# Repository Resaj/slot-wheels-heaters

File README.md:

# Slot wheels heaters
Wheels heaters for slot cars or line-following robots.

Each wheel heater carries a thermistor and is composed of an array of 25 resistor in parallel. The value of each resistance is 470 Ohm and the supply is a lipo battery 2S. Changing this values may burn the heaters, so if you change the values be sure the power consume values are right.

## Author
[Rubén Espino San José](https://github.com/Resaj)

## License

Todos estos productos están liberados mediante [Creative Commons Attribution-ShareAlike 4.0 International License](http://creativecommons.org/licenses/by-sa/4.0/).  
_All these products are released under [Creative Commons Attribution-ShareAlike 4.0 International License](http://creativecommons.org/licenses/by-sa/4.0/)._

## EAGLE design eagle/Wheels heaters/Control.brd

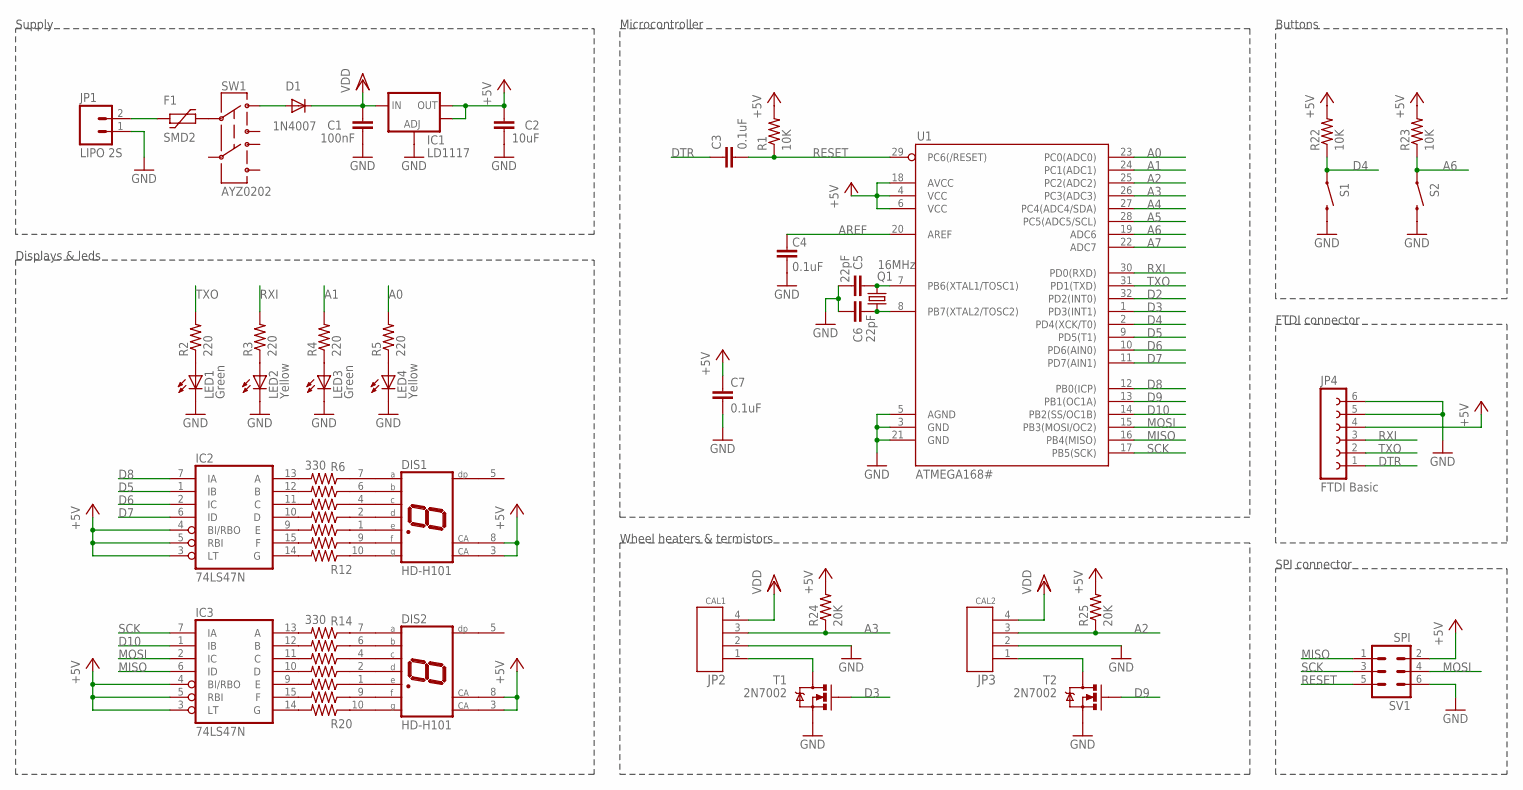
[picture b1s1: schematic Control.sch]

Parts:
C1: 100nF; C0805
C2: 10uF; C0805
C3, C4, C7: 0.1uF; C0805
C5, C6: 22pF; C0805
D1: 1N4007; SOD106-R
DIS1, DIS2: HD-H101; HDSP-M
F1: SMD2
IC1: LD1117; SOT223
IC2, IC3: 74LS47N; DIL16
JP1: LIPO 2S; 1X02
JP2: CAL1; 4_PINES_MACHO_TUMBADOS
JP3: CAL2; 4_PINES_MACHO_TUMBADOS
JP4: FTDI Basic; FE06W
LED1, LED3: Green; LED3MM
LED2, LED4: Yellow; LED3MM
Q1: 16MHz; HC49/S
R1, R22, R23: 10K; R0805
R2, R3, R4, R5: 220; R0805
R6, R7, R8, R9, R10, R11, R12, R14, R15, R16, R17, R18, R19, R20: 330; R0805
R24, R25: 20K; R0805
S1, S2: SWITCH-MOMENTARY-2PTH; TACTILE-PTH
SV1: SPI; MA03-2
SW1: AYZ0202
T1, T2: 2N7002; SOT23-3
U1: ATMEGA168#; TQFP32-08

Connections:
+5V: C2.1, C7.1, DIS1.3 (CA), DIS1.8 (CA), DIS2.3 (CA), DIS2.8 (CA), IC1.2 (OUT), IC1.4 (OUT), IC2.3 (LT), IC2.4 (BI/RBO), IC2.5 (RBI), IC2.16 (VCC), IC3.3 (LT), IC3.4 (BI/RBO), IC3.5 (RBI), IC3.16 (VCC), JP4.4, R1.2, R22.2, R23.2, R24.2, R25.2, SV1.2, U1.4 (VCC), U1.6 (VCC), U1.18 (AVCC)
A0: R5.2, U1.23 (PC0(ADC0))
A1: R4.2, U1.24 (PC1(ADC1))
A2: JP3.3, R25.1, U1.25 (PC2(ADC2))
A3: JP2.3, R24.1, U1.26 (PC3(ADC3))
A4: U1.27 (PC4(ADC4/SDA))
A5: U1.28 (PC5(ADC5/SCL))
A6: R23.1, S2.1, U1.19 (ADC6)
A7: U1.22 (ADC7)
AREF: C4.2, U1.20 (AREF)
D2: U1.32 (PD2(INT0))
D3: T1.1 (G), U1.1 (PD3(INT1))
D4: R22.1, S1.1, U1.2 (PD4(XCK/T0))
D5: IC2.1 (IB), U1.9 (PD5(T1))
D6: IC2.2 (IC), U1.10 (PD6(AIN0))
D7: IC2.6 (ID), U1.11 (PD7(AIN1))
D8: IC2.7 (IA), U1.12 (PB0(ICP))
D9: T2.1 (G), U1.13 (PB1(OC1A))
D10: IC3.1 (IB), U1.14 (PB2(SS/OC1B))
DTR: C3.1, JP4.1
GND: C1.1, C2.2, C4.1, C5.1, C6.1, C7.2, IC1.1 (ADJ), IC2.8 (GND), IC3.8 (GND), JP1.1, JP2.2, JP3.2, JP4.5, JP4.6, LED1.K (C), LED2.K (C), LED3.K (C), LED4.K (C), S1.3 (2), S2.3 (2), SV1.6, T1.2 (S), T2.2 (S), U1.3 (GND), U1.5 (AGND), U1.21 (GND)
MISO: IC3.6 (ID), SV1.1, U1.16 (PB4(MISO))
MOSI: IC3.2 (IC), SV1.4, U1.15 (PB3(MOSI/OC2))
unnamed: C6.2, Q1.2, U1.8 (PB7(XTAL2/TOSC2))
unnamed: C5.2, Q1.1, U1.7 (PB6(XTAL1/TOSC1))
unnamed: JP2.1, T1.3 (D)
unnamed: JP3.1, T2.3 (D)
unnamed: LED2.A, R3.1
unnamed: LED3.A, R4.1
unnamed: D1.A, SW1.3 (1)
unnamed: F1.P$2 (2), SW1.2
unnamed: F1.P$1 (1), JP1.2
unnamed: LED4.A, R5.1
unnamed: LED1.A, R2.1
unnamed: IC2.13 (A), R6.2
unnamed: DIS1.7 (A), R6.1
unnamed: IC2.12 (B), R7.2
unnamed: DIS1.6 (B), R7.1
unnamed: IC2.11 (C), R8.2
unnamed: DIS1.4 (C), R8.1
unnamed: IC2.10 (D), R9.2
unnamed: DIS1.2 (D), R9.1
unnamed: IC2.9 (E), R10.2
unnamed: DIS1.1 (E), R10.1
unnamed: IC2.15 (F), R11.2
unnamed: DIS1.9 (F), R11.1
unnamed: IC2.14 (G), R12.2
unnamed: DIS1.10 (G), R12.1
unnamed: IC3.13 (A), R14.2
unnamed: DIS2.7 (A), R14.1
unnamed: IC3.12 (B), R15.2
unnamed: DIS2.6 (B), R15.1
unnamed: IC3.11 (C), R16.2
unnamed: DIS2.4 (C), R16.1
unnamed: IC3.10 (D), R17.2
unnamed: DIS2.2 (D), R17.1
unnamed: IC3.9 (E), R18.2
unnamed: DIS2.1 (E), R18.1
unnamed: IC3.15 (F), R19.2
unnamed: DIS2.9 (F), R19.1
unnamed: IC3.14 (G), R20.2
unnamed: DIS2.10 (G), R20.1
RESET: C3.2, R1.1, SV1.5, U1.29 (PC6(/RESET))
RXI: JP4.3, R3.2, U1.30 (PD0(RXD))
SCK: IC3.7 (IA), SV1.3, U1.17 (PB5(SCK))
TXO: JP4.2, R2.2, U1.31 (PD1(TXD))
VDD: C1.2, D1.C, IC1.3 (IN), JP2.4, JP3.4

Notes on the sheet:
FTDI connector
Microcontroller
Displays & leds
Wheel heaters & termistors
Supply
Buttons
SPI connector

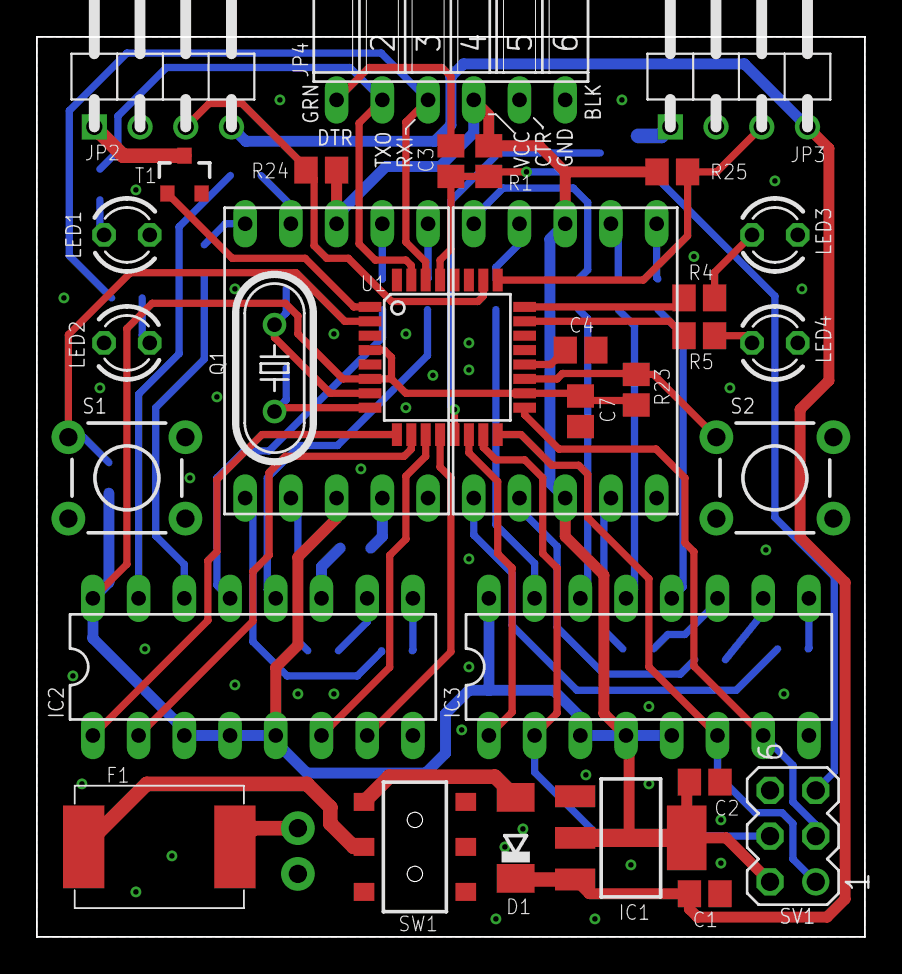
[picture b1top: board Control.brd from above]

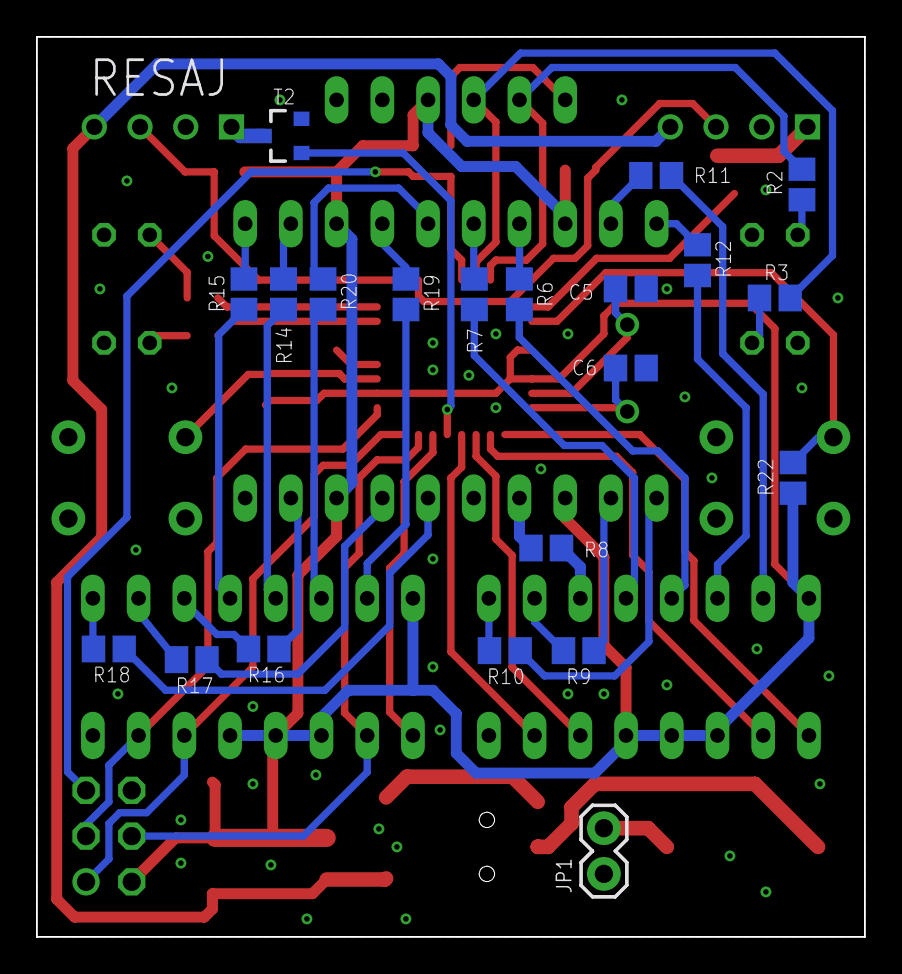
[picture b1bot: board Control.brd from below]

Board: 2 copper layers, 46.0 x 50.0 mm, 53 parts (21 on the bottom side), 63 nets.
